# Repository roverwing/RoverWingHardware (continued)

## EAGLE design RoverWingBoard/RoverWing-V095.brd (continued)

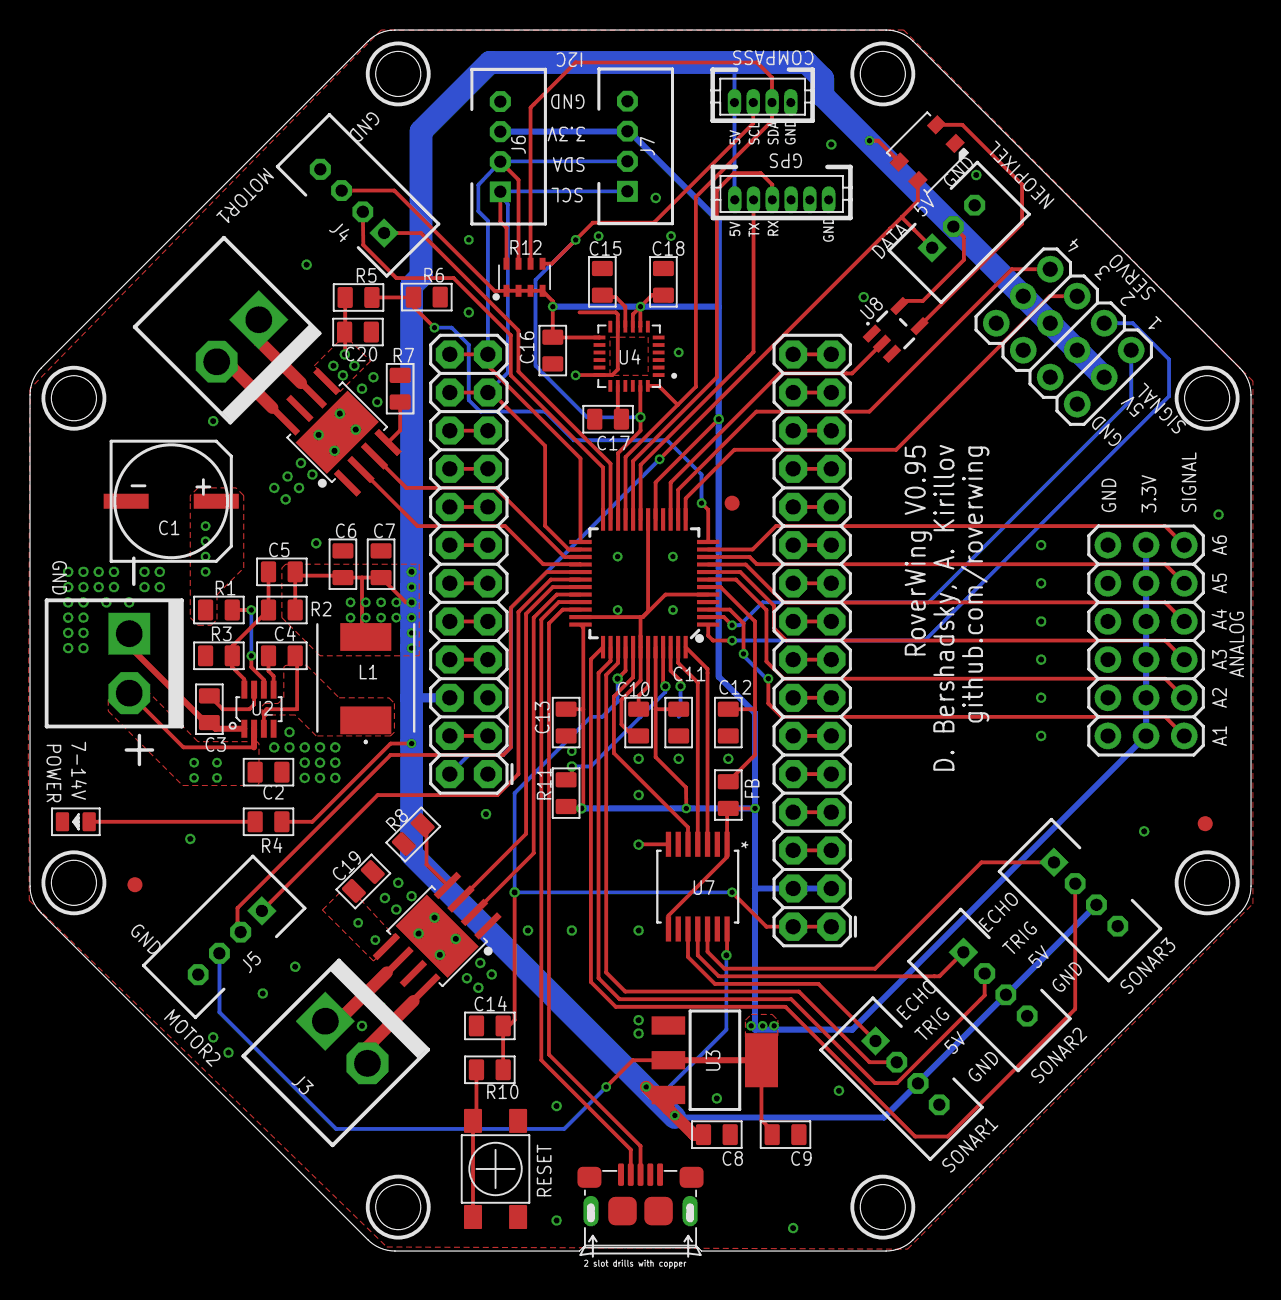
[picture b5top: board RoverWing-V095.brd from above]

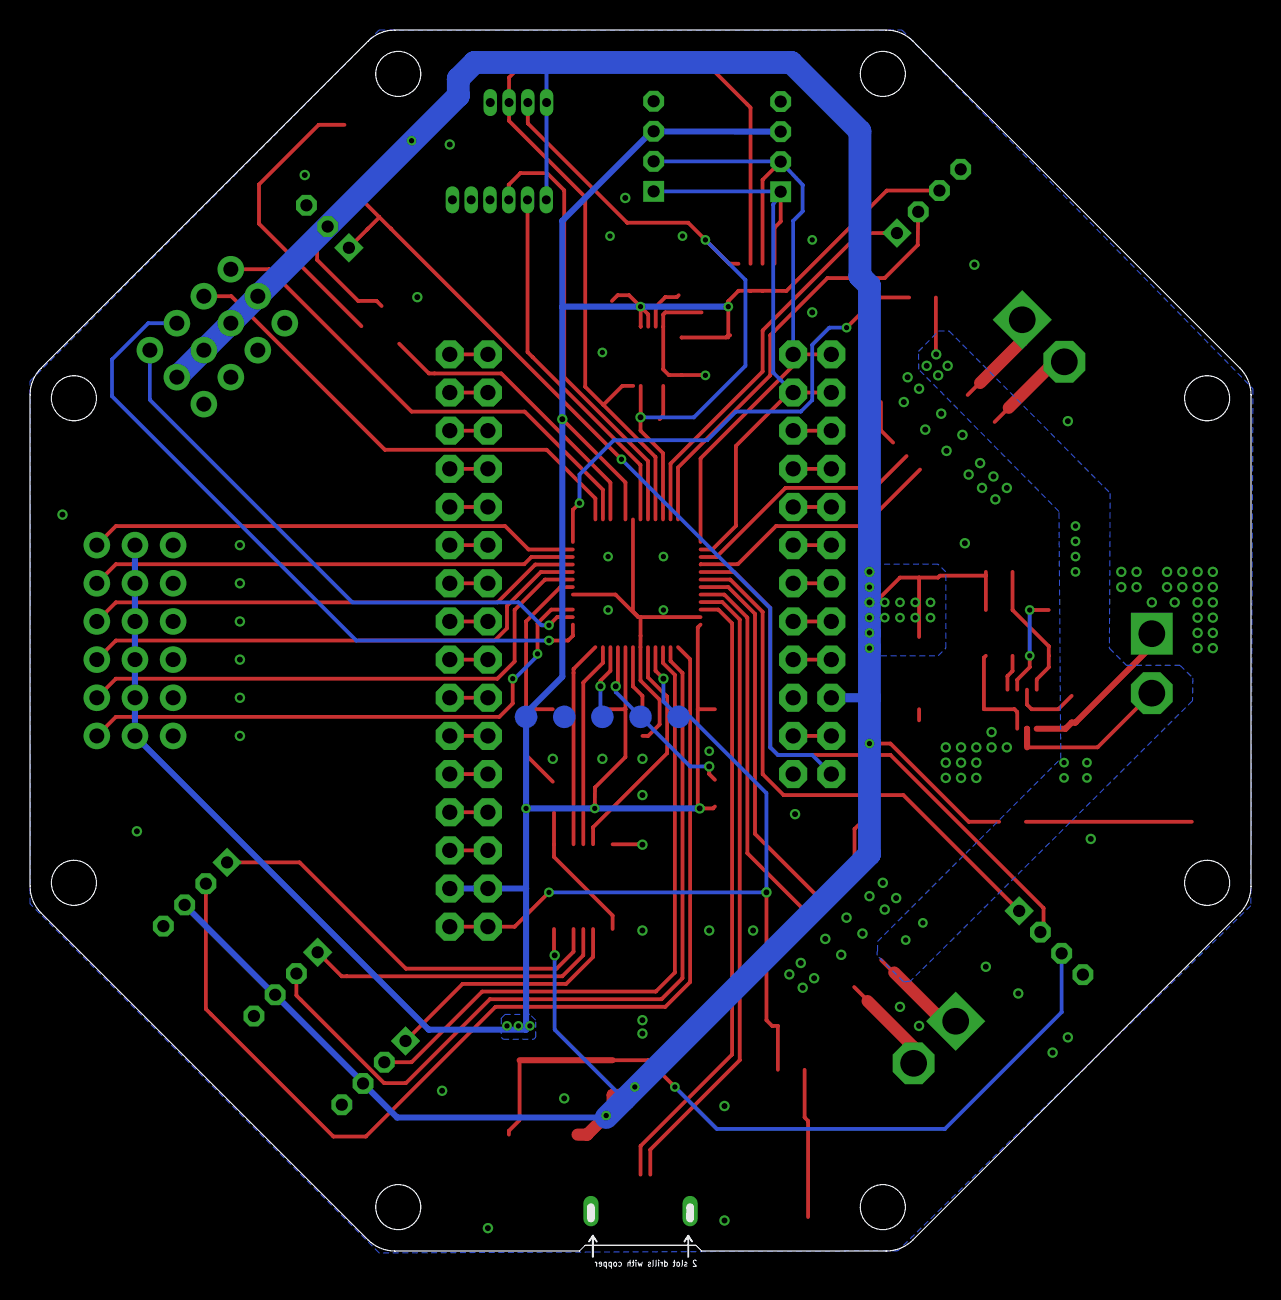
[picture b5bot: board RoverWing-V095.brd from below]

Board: 2 copper layers, 81.3 x 81.3 mm, 80 parts (5 on the bottom side), 84 nets.

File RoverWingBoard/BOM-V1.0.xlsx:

Parts | Qty | Value | Description | Part Num | Package | Mfg Name | Vendor | Vendor Part Num | Min quantity | Unit price | URL | Extended price
C1 | 1 | 220uF | CAP ALUM 220uF 20% 35V SMD | CK1V221MCRF10 | CAP-8X10.5 | Semtech | LCSC | C263948 | 5 | 7.2499999999999995E-2 | https://lcsc.com/product-detail/Others_Semtech-CKF1V221M0810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 | 7.2499999999999995E-2
C17 | 1 | 2.2nF | CAP CER 2.2NF 50V | C2012X7R1H222KT000N | 0805 | TDK | LCSC | C76647 | 50 | 1.52E-2 | https://lcsc.com/product-detail/Multilayer-Ceramic-Capacitor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 | 1.52E-2
C18 | 1 | 10nF | CAP CER 10NF 100V | CL21B103KCANNNC | 0805 | Samsung Electro-Mechanics | LCSC | C18741 | 50 | 1.35E-2 | https://lcsc.com/product-detail/Multilayer-Ceramic-Capacitor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 | 1.35E-2
C2, C6, C7 | 3 | 22uF | CAP CER 22uF 25V X5R | CL21A226MAQNNNE | 0805 | Samsung Electro-Mechanics | LCSC | C45783 | 5 | 0.12239999999999999 | https://lcsc.com/product-detail/Multilayer-Ceramic-Capacitor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 | 0.36719999999999997
C3, C4, C11, C12, C13, C14, C15, C16, C19, C20 | 10 | 100nF | CAP CER 0.1UF 50V | 0805B104M500NT | 0805 | Guangdong Fenghua Advanced Tech | LCSC | C286511 | 50 | 1.6899999999999998E-2 | https://lcsc.com/product-detail/Others_Guangdong-Fenghua-Adv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 | 0.16899999999999998
C5 | 1 | 33pF | CAP CER 33pF 50V | CL21C330JBANNNC | 0805 | Samsung Electro-Mechanics | LCSC | C1814 | 50 | 1.23E-2 | https://lcsc.com/product-detail/Multilayer-Ceramic-Capacitor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 | 1.23E-2
C8, C9, C10 | 3 | 1uF | CAP CER 1uF 25V | 0805B105K250AT | 0805 | Guangdong Fenghua Advanced Tech | LCSC | C111769 | 20 | 2.0299999999999999E-2 | https://lcsc.com/product-detail/Multilayer-Ceramic-Capacitor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 | 6.0899999999999996E-2
D1 | 1 | GREEN | Light Emitting Diodes (LED) Green 567.5~576.5nm 18~71mcd@20mA Top View 0805 RoHS | LTST-C170KGKT | LED-0805 | Lite-On | LCSC | C98221 | 20 | 2.76E-2 | https://lcsc.com/product-detail/Light-Emitting-Diodes-LED_LT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 | 2.76E-2
FB | 1 | 330R-1500MA | FERRITE BEAD 330 OHM 0805 1LN | BLM21PG331SN1D | 0805 | Murata Electronics | LCSC | C74764 | 20 | 3.5099999999999999E-2 | https://lcsc.com/product-detail/Ferrite-Beads-And-Chips_muRa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 | 3.5099999999999999E-2
J1, J2, J3 | 3 | HEADER-VH | CONN HEADER VH TOP 2POS 3.96MM | B2P-VH(LF)(SN) | B2P-VH | JST Sales America | LCSC | C160315 | 5 | 6.6799999999999998E-2 | * | 0.20039999999999999
J11 | 1 | HEADER-PH-3P | CONN HEADER PH TOP 3POS 2MM | B3B-PH-K-S(LF)(SN) | B3B-PH-K | JST Sales America | LCSC | C131339 | 5 | 9.9699999999999997E-2 | https://lcsc.com/product-detail/PCB-Connectors-Headers-Male-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 | 9.9699999999999997E-2
J12 | 1 | HEADER-3X04 | * | * | 3X04 | * | * | * | * | * | *
J13 | 1 | HEADER-3X06 | * | * | 3X06 | * | * | * | * | * | *
J14 | 1 | HEADER-2X16 | FEMALE HEADER 2*16 2.54MM | DS1023-2*16SF11 | 2X16 | CONNFLY Elec | LCSC | C132130 | 1 | 0.1454 | https://lcsc.com/product-detail/Female-Header_DS1023-2-16SF1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 | 0.1454
J15 | 1 | HEADER-2X12 | FEMALE HEADER 2*12 2.54MM | DS1023-2*12SF11 | 2X12 | CONNFLY Elec | LCSC | C92265 | 1 | 0.1201 | https://lcsc.com/product-detail/Female-Header_2-54Female-hea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 | 0.1201
J16 | 1 | DF13-4P-1.25DSA | CONN HEADER DF13 4POS 1.25MM | DF13-4P-1.25DSA | DF13-4P-1.25DSA | Hirose | LCSC | C202091 | 1 | 0.26550000000000001 | https://lcsc.com/product-detail/Connectors_Hirose_DF13-4P-1-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 | 0.26550000000000001
J17 | 1 | DF13-6P-1.25DSA | CONN HEADER DF13 6POS 1.25MM | DF13-6P-1.25DSA | DF13-6P-1.25DSA | Hirose | Digikey | H2195-ND | 1 | 0.33 | https://www.digikey.com/product-detail/en/hirose-electric-co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 | 0.33
J4, J5, J6, J7, J8, J9, J10 | 7 | HEADER-PH-4P | CONN HEADER PH TOP 4POS 2MM | B4B-PH-K-S(LF)(SN) | B4B-PH-K | JST Sales America | LCSC | C160257 | 10 | 5.91E-2 | https://lcsc.com/product-detail/Wire-To-Board-Wire-To-Wire-C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 | 0.41370000000000001
L1 | 1 | 4.7uH | Power Inductors 4.7uH Â±20% 5.6A | SPM6530T-4R7M | IND_TDK_7.1X6.5 | TDK | LCSC | C76857 | 10 | 0.1082 | https://lcsc.com/product-detail/Power-Inductors_TDK_SPM6530T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 | 0.1082
LED1 | 1 | WS2812B3535 | SMART LED, 3.5MM SMD | WS2812B-3535 | LED3535 | Worldsemi | LCSC | C114583 | 5 | 0.1145 | https://lcsc.com/product-detail/Light-Emitting-Diodes-LED_35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 | 0.1145
R1, R5 | 2 | 100k | RES SMD 100K OHM 1% | RC0805FR-07100KL | 0805 | YAGEO | LCSC | C96346 | 50 | 5.4000000000000003E-3 | https://lcsc.com/product-detail/Chip-Resistor-Surface-Mount_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 | 1.0800000000000001E-2
R11 | 1 | 2.7k*4 | Resistor Networks & Arrays 2.7KOhms Â±5% 1/16W 0603_x4 | RTA03-4D272JTP | 0603*4 | RALEC | LCSC | C102660 | 50 | 8.6999999999999994E-3 | https://lcsc.com/product-detail/Resistor-Networks-Arrays_2-7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 | 8.6999999999999994E-3
R2 | 1 | 40.2k | RES SMD 40.2KOhms ±1% 1/8W 0805 RoHS | RC0805FR-0740K2L | 0805 | YAGEO | LCSC | C273827 | 100 | 2.3999999999999998E-3 | https://lcsc.com/product-detail/Others_YAGEO-RC0805FR-0740K2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 | 2.3999999999999998E-3
R3 | 1 | 5.49 | RES SMD 5.49KOhms ±1% 1/8W 0805 RoHS | RC0805FR-075K49L | 0805 | YAGEO | LCSC | C273977 | 50 | 3.8E-3 | https://lcsc.com/product-detail/Others_YAGEO-RC0805FR-075K49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 | 3.8E-3
R4, R10, R109 | 3 | 1k | RES SMD 1K OHMs Â±5% 1/8W | RC0805JR-071KL | 0805 | YAGEO | LCSC | C100046 | 50 | 2.7000000000000001E-3 | https://lcsc.com/product-detail/Chip-Resistor-Surface-Mount_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 | 8.0999999999999996E-3
R6, R7, R8 | 3 | 22k | RES SMD 22KOhms Â±1% | RC0805FR-0722KL | 0805 | YAGEO | LCSC | C114565 | 50 | 4.3E-3 | https://lcsc.com/product-detail/Chip-Resistor-Surface-Mount_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 | 1.29E-2
SW1 | 1 | SW-TACTILE-4.5X4.5_SMD | Tactile Switches SPST 4.50mm x 4.50mm 0.90mm 50mA @ 12VDC SMD RoHS | TSA453G38-250 | TL3305 | BRIGHT | LCSC | C294494 | 20 | 2.5399999999999999E-2 | https://lcsc.com/product-detail/Tactile-Switches_BRIGHT-TSA4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 | 2.5399999999999999E-2
U1 | 1 | ATSAMD21G | IC MCU 32BIT 256KB FLASH 48TQFP | ATSAMD21G18A-AU | TQFP-48-EDITED | Microchip Technology | Digikey | ATSAMD21G18A-AU-ND | 1 | 3.22 | https://www.digikey.com/product-detail/en/microchip-technolo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 | 3.22
U2 | 1 | PMIC-MP2225 | DC-DC Converters Step-Down Adjustable 1 4.5V 18V 0.6V 17V 5A TSOT-23-8Â | MP2225GJ-Z | SOT-23-8 | Monolithic Power Systems | LCSC | C133066 | 10 | 0.32140000000000002 | https://lcsc.com/product-detail/DC-DC-Converters_MPS_MP2225G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 | 0.32140000000000002
U3 | 1 | AZ1117EH-3.3 | Low Dropout Regulators(LDO) Positive Fixed 1.3V @ 1A 13V 3.3V 1AÂ | AZ1117EH-3.3TRG1 | SOT223 | Diodes Inc | LCSC | C108494 | 5 | 8.1299999999999997E-2 | https://lcsc.com/product-detail/Low-Dropout-Regulators-LDO_D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 | 8.1299999999999997E-2
U4 | 1 | MPU-6050 | IMU ACCEL/GYRO 3-AXIS I2C 24QFN | MPU-6050 | QFN50P400X400X95-24N | TDK InvenSense | LCSC | C24112 | 1 | 2.8835000000000002 | https://lcsc.com/product-detail/Attitude-Sensors_TDK-InvenSe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 | 2.8835000000000002
U5, U6 | 2 | DRV8871 | Motor Drivers SO-8 RoHS | DRV8871DDAR | HSOP8 | Texas Instruments | LCSC | C75864 | 1 | 1.7250000000000001 | https://lcsc.com/product-detail/Motor-Drivers_TI_DRV8871DDAR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 | 3.45
U7 | 1 | TXS0104EPWR | Level Translators, Shifters TSSOP-14 RoHS | TXS0104EPWR | PW14 | Texas Instruments | LCSC | C44955 | 1 | 0.69340000000000002 | https://lcsc.com/product-detail/Interface-ICs_TI_TXS0104EPWR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 | 0.69340000000000002
U8 | 1 | 74AHCT1G125DBV | 74 Series Buffer, Non-Inverting 4.5V ~ 5.5V SOT-23-5 RoHS | SN74AHCT1G125DBVR | SOT23-5 | Texas Instruments | LCSC | C7484 | 5 | 0.12809999999999999 | https://lcsc.com/product-detail/74-Series_TI_SN74AHCT1G125DB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 | 0.12809999999999999
USB1 | 1 | MICRO-USB-SMD-B-(10118193-0001LF) | CONN USB MICRO B RECPT SMT R/A | 10118193-0001LF | MICRO-USB5+6P-SMD-0.65-B | Amphenol ICC | LCSC | C132562 | 1 | 0.24 | https://lcsc.com/product-detail/USB-Connectors_Amphenol_1011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 | 0.24
Total price
